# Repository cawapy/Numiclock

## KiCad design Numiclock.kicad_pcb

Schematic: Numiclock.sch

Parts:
J101: Barrel_Jack_Switch; BARREL_JACK
R101: 150; R_0805_HandSoldering
R102: 100; R_0805_HandSoldering
R103, R104: 10k; R_0805_HandSoldering
U101: AMS1117; SOT-223
U102: DCF1

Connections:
/DigitA/~OE: R103.2; also elsewhere on the board
/DigitA/~SRCLR: R104.2; also elsewhere on the board
GND: J101.2, R101.2, U102.3; also elsewhere on the board
unnamed: R101.1, R102.2, U101.1 (ADJ)
VCC: J101.1, R103.1, R104.1, U101.3 (VI); also elsewhere on the board
VD: R102.1, U101.2 (VO), U102.4; also elsewhere on the board

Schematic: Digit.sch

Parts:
C201: 0μ1; C_0805_HandSoldering
DS201: IV-9
U201: 74HC595; SOIC-16_3.9x9.9mm_Pitch1.27mm
U202: ULN2803A; SOIC-18W_7.5x11.6mm_Pitch1.27mm

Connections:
/DigitA/CASC: U201.9 (QH'); also elsewhere on the board
/DigitA/RCLK: U201.12 (RCLK); also elsewhere on the board
/DigitA/SER: U201.14 (SER)
/DigitA/SRCLK: U201.11 (SRCLK); also elsewhere on the board
/DigitA/~OE: U201.13 (~OE); also elsewhere on the board
/DigitA/~SRCLR: U201.10 (~SRCLR); also elsewhere on the board
GND: C201.1, U201.8 (GND), U202.9 (GND); also elsewhere on the board
unnamed: DS201.2, U202.18 (O1)
unnamed: DS201.3, U202.17 (O2)
unnamed: DS201.4, U202.16 (O3)
unnamed: DS201.5, U202.15 (O4)
unnamed: DS201.6, U202.14 (O5)
unnamed: DS201.7, U202.13 (O6)
unnamed: DS201.8, U202.12 (O7)
unnamed: DS201.9, U202.11 (O8)
unnamed: U201.1 (QB), U202.7 (I7)
unnamed: U201.2 (QC), U202.6 (I6)
unnamed: U201.3 (QD), U202.5 (I5)
unnamed: U201.4 (QE), U202.4 (I4)
unnamed: U201.5 (QF), U202.3 (I3)
unnamed: U201.6 (QG), U202.2 (I2)
unnamed: U201.7 (QH), U202.1 (I1)
unnamed: U201.15 (QA), U202.8 (I8)
VCC: C201.2, U201.16 (VCC); also elsewhere on the board
VD: DS201.1, U202.10 (COM); also elsewhere on the board

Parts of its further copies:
C301, C401, C501: 0μ1; C_0805_HandSoldering
DS301, DS401, DS501: IV-9
U301, U401, U501: 74HC595; SOIC-16_3.9x9.9mm_Pitch1.27mm
U302, U402, U502: ULN2803A; SOIC-18W_7.5x11.6mm_Pitch1.27mm

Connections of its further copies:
/DigitA/CASC: U301.14 (SER); also elsewhere on the board
/DigitA/RCLK: U301.12 (RCLK), U401.12 (RCLK), U501.12 (RCLK); also elsewhere on the board
/DigitA/SRCLK: U301.11 (SRCLK), U401.11 (SRCLK), U501.11 (SRCLK); also elsewhere on the board
/DigitA/~OE: U301.13 (~OE), U401.13 (~OE), U501.13 (~OE); also elsewhere on the board
/DigitA/~SRCLR: U301.10 (~SRCLR), U401.10 (~SRCLR), U501.10 (~SRCLR); also elsewhere on the board
/DigitB/CASC: U301.9 (QH'), U401.14 (SER)
/DigitC/CASC: U401.9 (QH'), U501.14 (SER)
/DigitD/CASC: U501.9 (QH')
GND: C301.1, C401.1, C501.1, U301.8 (GND), U302.9 (GND), U401.8 (GND), U402.9 (GND), U501.8 (GND), U502.9 (GND); also elsewhere on the board
unnamed: DS301.2, U302.18 (O1)
unnamed: DS301.3, U302.17 (O2)
unnamed: DS301.4, U302.16 (O3)
unnamed: DS301.5, U302.15 (O4)
unnamed: DS301.6, U302.14 (O5)
unnamed: DS301.7, U302.13 (O6)
unnamed: DS301.8, U302.12 (O7)
unnamed: DS301.9, U302.11 (O8)
unnamed: DS401.2, U402.18 (O1)
unnamed: DS401.3, U402.17 (O2)
unnamed: DS401.4, U402.16 (O3)
unnamed: DS401.5, U402.15 (O4)
unnamed: DS401.6, U402.14 (O5)
unnamed: DS401.7, U402.13 (O6)
unnamed: DS401.8, U402.12 (O7)
unnamed: DS401.9, U402.11 (O8)
unnamed: DS501.2, U502.18 (O1)
unnamed: DS501.3, U502.17 (O2)
unnamed: DS501.4, U502.16 (O3)
unnamed: DS501.5, U502.15 (O4)
unnamed: DS501.6, U502.14 (O5)
unnamed: DS501.7, U502.13 (O6)
unnamed: DS501.8, U502.12 (O7)
unnamed: DS501.9, U502.11 (O8)
unnamed: U301.1 (QB), U302.7 (I7)
unnamed: U301.2 (QC), U302.6 (I6)
unnamed: U301.3 (QD), U302.5 (I5)
unnamed: U301.4 (QE), U302.4 (I4)
unnamed: U301.5 (QF), U302.3 (I3)
unnamed: U301.6 (QG), U302.2 (I2)
unnamed: U301.7 (QH), U302.1 (I1)
unnamed: U301.15 (QA), U302.8 (I8)
unnamed: U401.1 (QB), U402.7 (I7)
unnamed: U401.2 (QC), U402.6 (I6)
unnamed: U401.3 (QD), U402.5 (I5)
unnamed: U401.4 (QE), U402.4 (I4)
unnamed: U401.5 (QF), U402.3 (I3)
unnamed: U401.6 (QG), U402.2 (I2)
unnamed: U401.7 (QH), U402.1 (I1)
unnamed: U401.15 (QA), U402.8 (I8)
unnamed: U501.1 (QB), U502.7 (I7)
unnamed: U501.2 (QC), U502.6 (I6)
unnamed: U501.3 (QD), U502.5 (I5)
unnamed: U501.4 (QE), U502.4 (I4)
unnamed: U501.5 (QF), U502.3 (I3)
unnamed: U501.6 (QG), U502.2 (I2)
unnamed: U501.7 (QH), U502.1 (I1)
unnamed: U501.15 (QA), U502.8 (I8)
VCC: C301.2, C401.2, C501.2, U301.16 (VCC), U401.16 (VCC), U501.16 (VCC); also elsewhere on the board
VD: DS301.1, DS401.1, DS501.1, U302.10 (COM), U402.10 (COM), U502.10 (COM); also elsewhere on the board

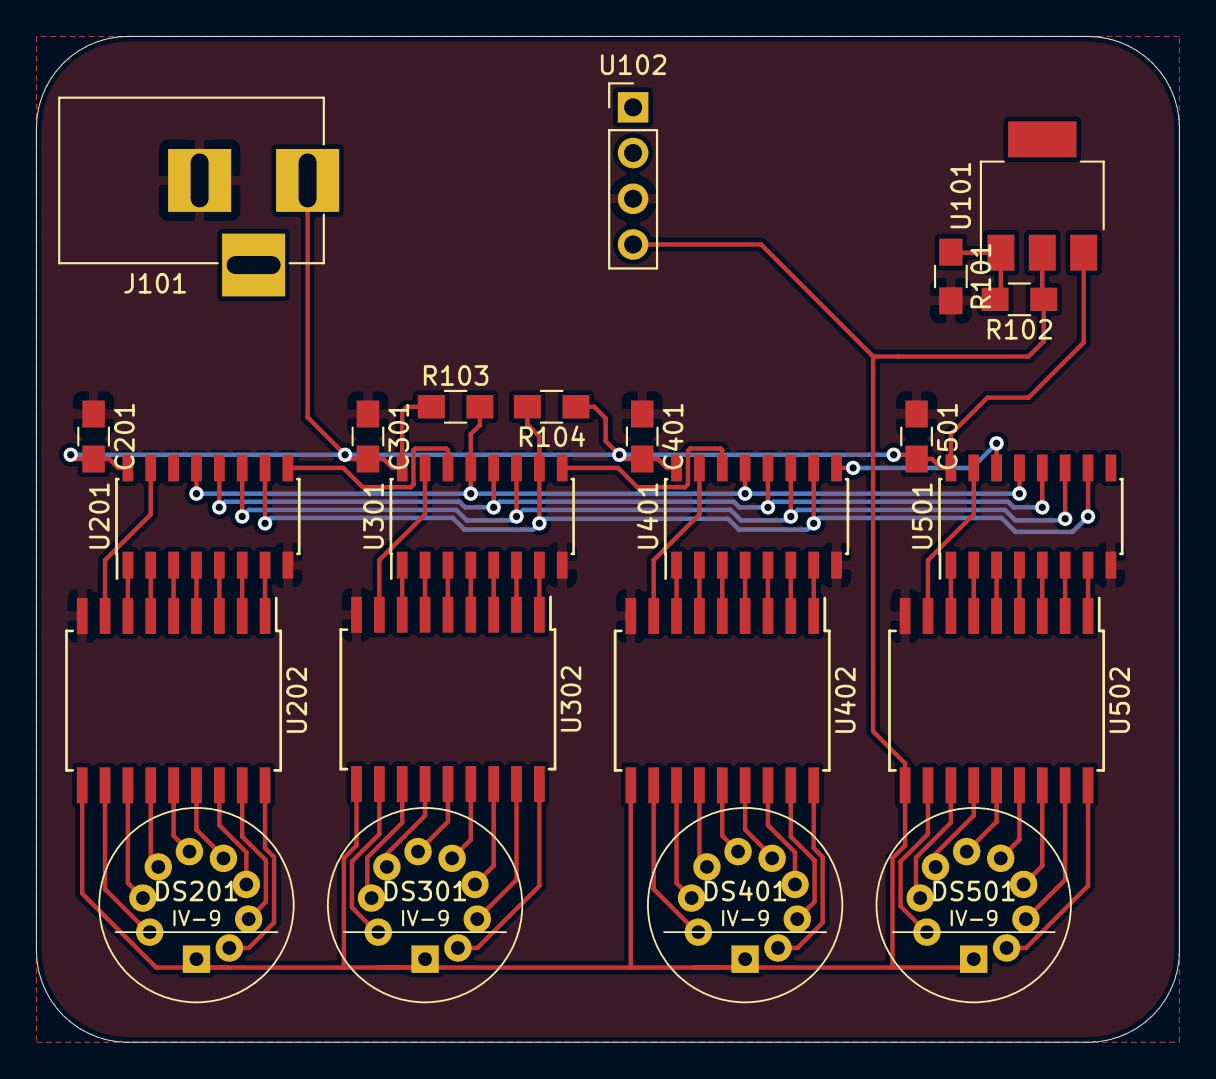
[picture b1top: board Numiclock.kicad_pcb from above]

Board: 2 copper layers, 63.5 x 55.9 mm, 23 parts (0 on the bottom side), 75 nets.

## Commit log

2019-06-23 Initial commit with external KiCadLib
2019-06-23 Adding empty KiCad project
2019-06-23 Starting Numiclock
2019-06-23 Rearrange partial circuit
2019-06-23 ignore fp-info-cache
2019-06-23 Using hierarchical schematics for each digit unit; include IV-9 footprint
2019-06-23 Update packages
2019-06-24 Flip HC595 - ULN2803 pin mapping for easier routing
2019-06-24 adding partial pcb
2019-06-24 using kicadlib with newer 3d model
2019-06-25 adding atmega328p-au
